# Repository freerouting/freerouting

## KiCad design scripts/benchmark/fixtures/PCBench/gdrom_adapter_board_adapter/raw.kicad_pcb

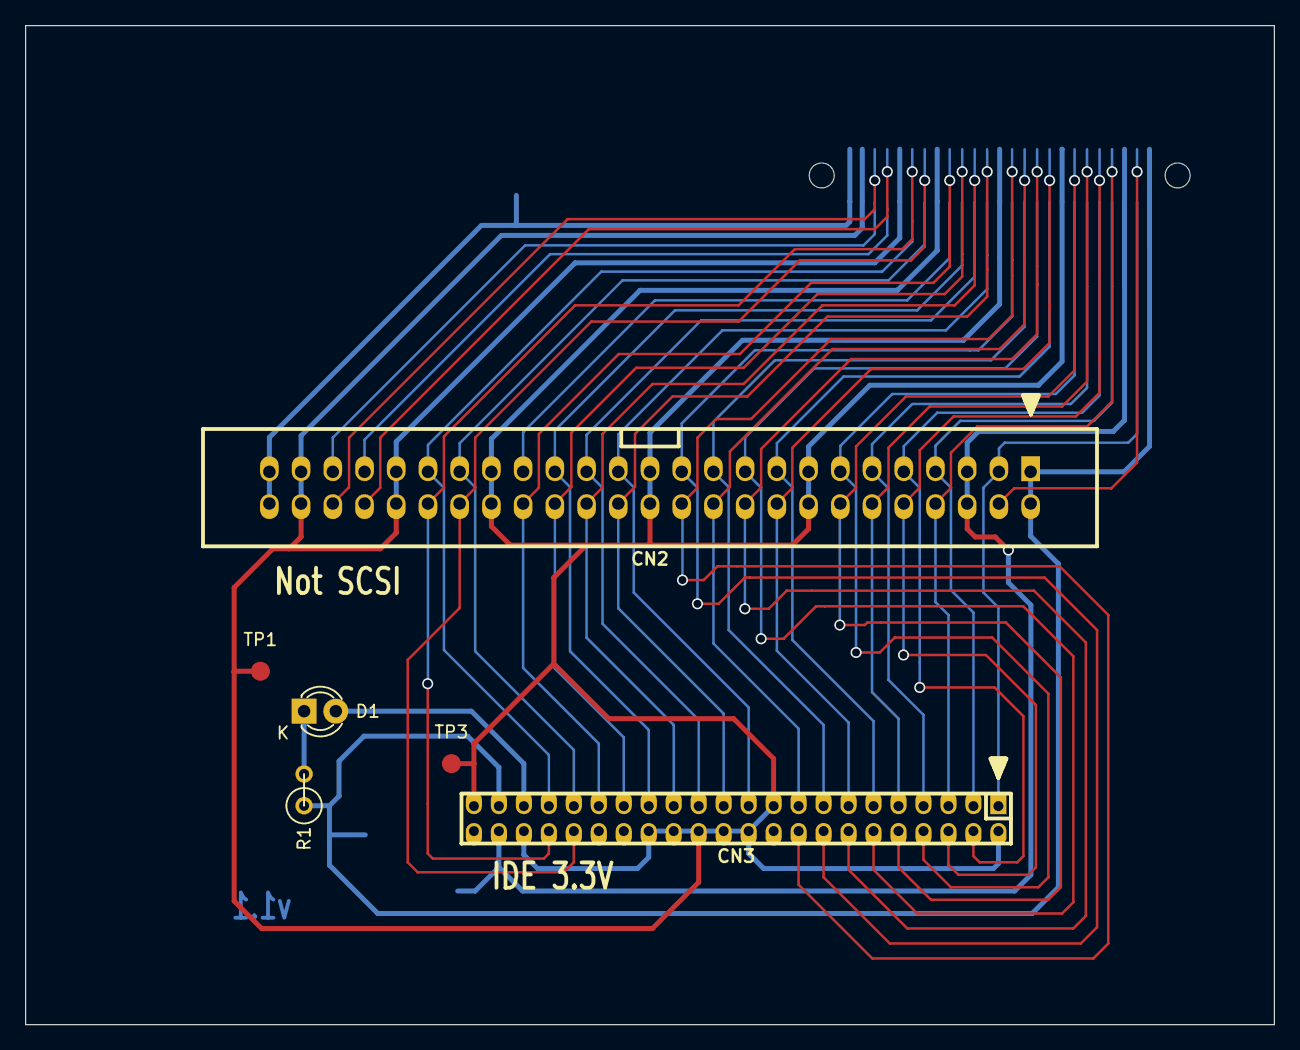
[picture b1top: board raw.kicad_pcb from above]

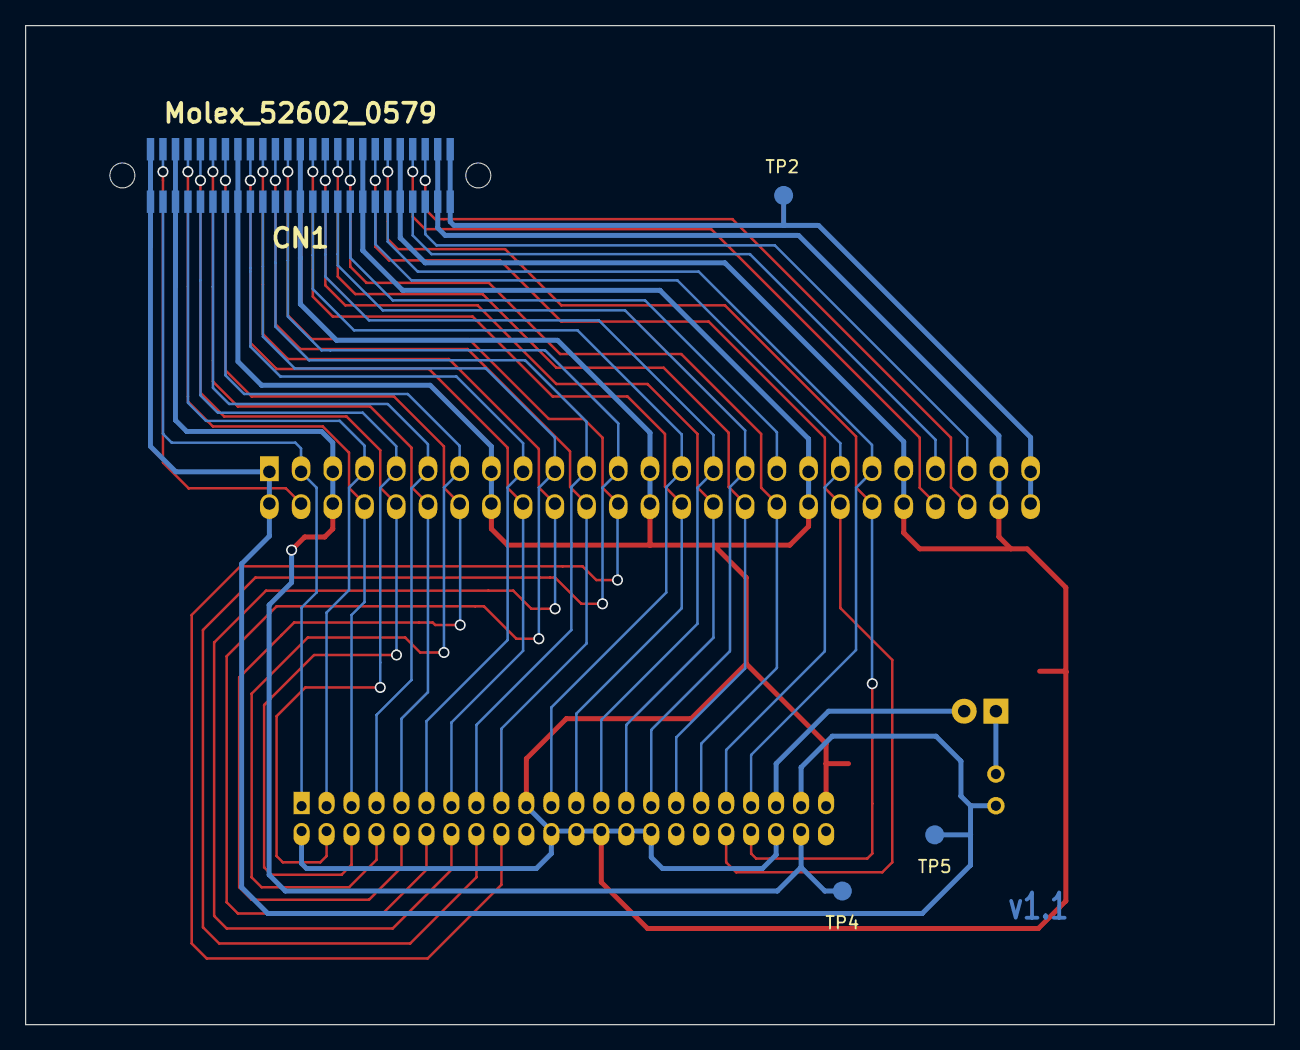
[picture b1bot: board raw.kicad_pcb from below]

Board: 2 copper layers, 100.0 x 80.0 mm, 10 parts (4 on the bottom side), 40 nets.

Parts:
CN1: Molex_52602_0579
CN2: CONN_25X2; vasch_strip_25x2
CN3: CONN_02X22; pin_strip_2mm_22x2
D1: LED; LED-3MM
R1: 1k; R1
TP1, TP2, TP3, TP4, TP5: Measurement_Point_Round-SMD-Pad_Small

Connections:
+3V3: CN1.A1, CN1.B1, CN2.1, CN2.2, CN3.41, R1.1, TP5.1
+5V: CN1.A3, CN1.B3, CN2.5, CN2.6, CN3.42, TP4.1
+12V: CN1.A25, CN1.B25, CN2.49, CN2.50, TP2.1
/A0: CN1.A19, CN2.37, CN3.35
/A1: CN1.B17, CN2.34, CN3.33
/A2: CN1.B19, CN2.38, CN3.36
/ACTIVEn: CN3.39, D1.2
/CD_CLK: CN1.B23, CN2.46
/CS0n: CN1.A20, CN2.39, CN3.37
/CS1n: CN1.B20, CN2.40, CN3.38
/D0: CN1.B11, CN2.22, CN3.17
/D1: CN1.A11, CN2.21, CN3.15
/D2: CN1.B9, CN2.18, CN3.13
/D3: CN1.A9, CN2.17, CN3.11
/D4: CN1.B6, CN2.12, CN3.9
/D5: CN1.A6, CN2.11, CN3.7
/D6: CN1.B4, CN2.8, CN3.5
/D7: CN1.A4, CN2.7, CN3.3
/D8: CN1.A5, CN2.9, CN3.4
/D9: CN1.B5, CN2.10, CN3.6
/D10: CN1.A7, CN2.13, CN3.8
/D11: CN1.B7, CN2.14, CN3.10
/D12: CN1.A10, CN2.19, CN3.12
/D13: CN1.B10, CN2.20, CN3.14
/D14: CN1.A12, CN2.23, CN3.16
/D15: CN1.B12, CN2.24, CN3.18
/DMACKn: CN1.A16, CN2.31, CN3.29
/DMARQ: CN1.A14, CN2.27, CN3.21
/EMPH: CN1.A17, CN2.33
/G_RST: CN1.A2, CN2.3, CN3.1
/INTRQ: CN1.B16, CN2.32, CN3.31
/IORDY: CN1.B15, CN2.30, CN3.27
/LRCK: CN1.B22, CN2.44
/RDn: CN1.A15, CN2.29, CN3.25
/SCK: CN1.A22, CN2.43
/SDAT: CN1.A23, CN2.45
/WRn: CN1.B14, CN2.28, CN3.23
/xB2: CN1.B2, CN2.4
GND: CN1.A8, CN1.A13, CN1.A18, CN1.A21, CN1.A24, CN1.B8, CN1.B13, CN1.B18, CN1.B21, CN1.B24, CN2.15, CN2.16, CN2.25, CN2.26, CN2.35, CN2.36, CN2.41, CN2.42, CN2.47, CN2.48, CN3.2, CN3.19, CN3.22, CN3.24, CN3.26, CN3.28, CN3.30, CN3.40, CN3.43, TP1.1, TP3.1
unnamed: D1.1, R1.2

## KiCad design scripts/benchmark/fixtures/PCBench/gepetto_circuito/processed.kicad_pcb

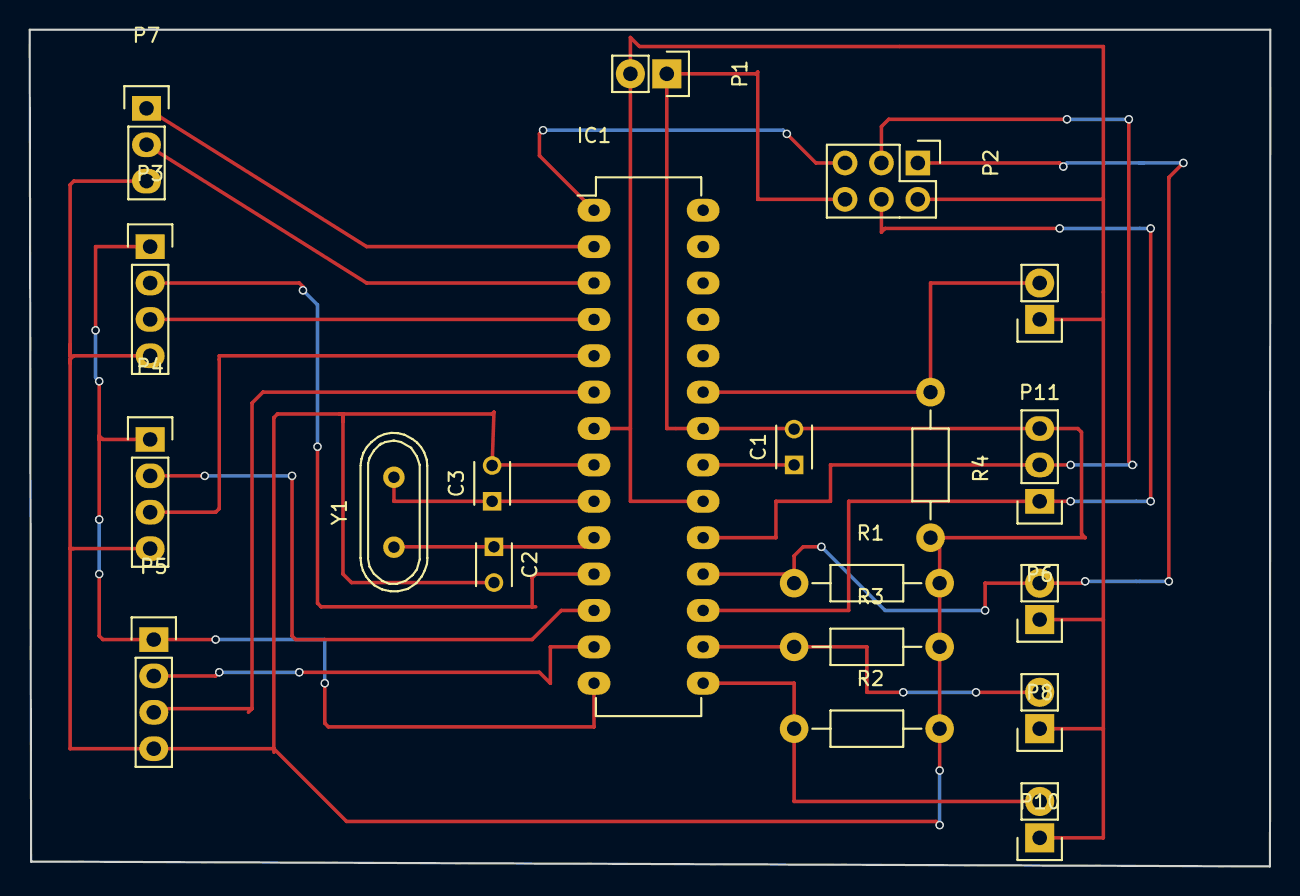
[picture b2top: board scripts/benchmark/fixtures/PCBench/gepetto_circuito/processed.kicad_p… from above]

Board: 2 copper layers, 86.6 x 58.4 mm, 20 parts (0 on the bottom side), 21 nets.

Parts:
C1: 100n; C_Disc_D3_P2.5
C2, C3: 22 pF; C_Disc_D3_P2.5
IC1: ATMEGA328-P; DIP-28_W7.62mm_LongPads
P1: CONN_5V; Pin_Header_Straight_1x02
P2: CONN_02X03; Pin_Header_Straight_2x03
P3: CONN_EJE_X; Pin_Header_Straight_1x04
P4: CONN_EJE_Y; Pin_Header_Straight_1x04
P5: CONN_EJE_Z; Pin_Header_Straight_1x04
P6: CONN_HUS; Pin_Header_Straight_1x03
P7: CONN_UART; Pin_Header_Straight_1x03
P8: CONN_LIM_Z; Pin_Header_Straight_1x02
P9: CONN_LIM_X; Pin_Header_Straight_1x02
P10: CONN_LIM_Y; Pin_Header_Straight_1x02
P11: CONN_E_STOP; Pin_Header_Straight_1x02
R1, R2, R3, R4: 15 k; Resistor_Horizontal_RM10mm
Y1: 16Mhz; Crystal_HC49-U_Vertical

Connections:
/MISO: IC1.18, P2.1, P8.2, R1.1
/MOSI: IC1.17, P2.4, P6.1
/RESET: IC1.1, P2.5
/Rx_int: IC1.2, P7.1
/SCK: IC1.19, P2.3, P6.2
/Tx_int: IC1.3, P7.2
/button_stop: IC1.23, P11.2, R4.1
/dir_X: IC1.11, P3.2
/dir_Y: IC1.12, P4.2
/dir_Z: IC1.13, P5.2
/enable: IC1.14, P3.1, P4.1, P5.1
/lim_X: IC1.15, P9.2, R2.1
/lim_Y: IC1.16, P10.2, R3.1
/step_X: IC1.4, P3.3
/step_Y: IC1.5, P4.3
/step_Z: IC1.6, P5.3
GND: C1.2, C2.2, C3.2, IC1.8, IC1.22, P1.1, P2.6, P3.4, P4.4, P5.4, P6.3, P7.3, R1.2, R2.2, R3.2, R4.2
unnamed: C1.1, IC1.21
unnamed: C2.1, IC1.10, Y1.1
unnamed: C3.1, IC1.9, Y1.2
VCC: IC1.7, IC1.20, P1.2, P2.2, P8.1, P9.1, P10.1, P11.1

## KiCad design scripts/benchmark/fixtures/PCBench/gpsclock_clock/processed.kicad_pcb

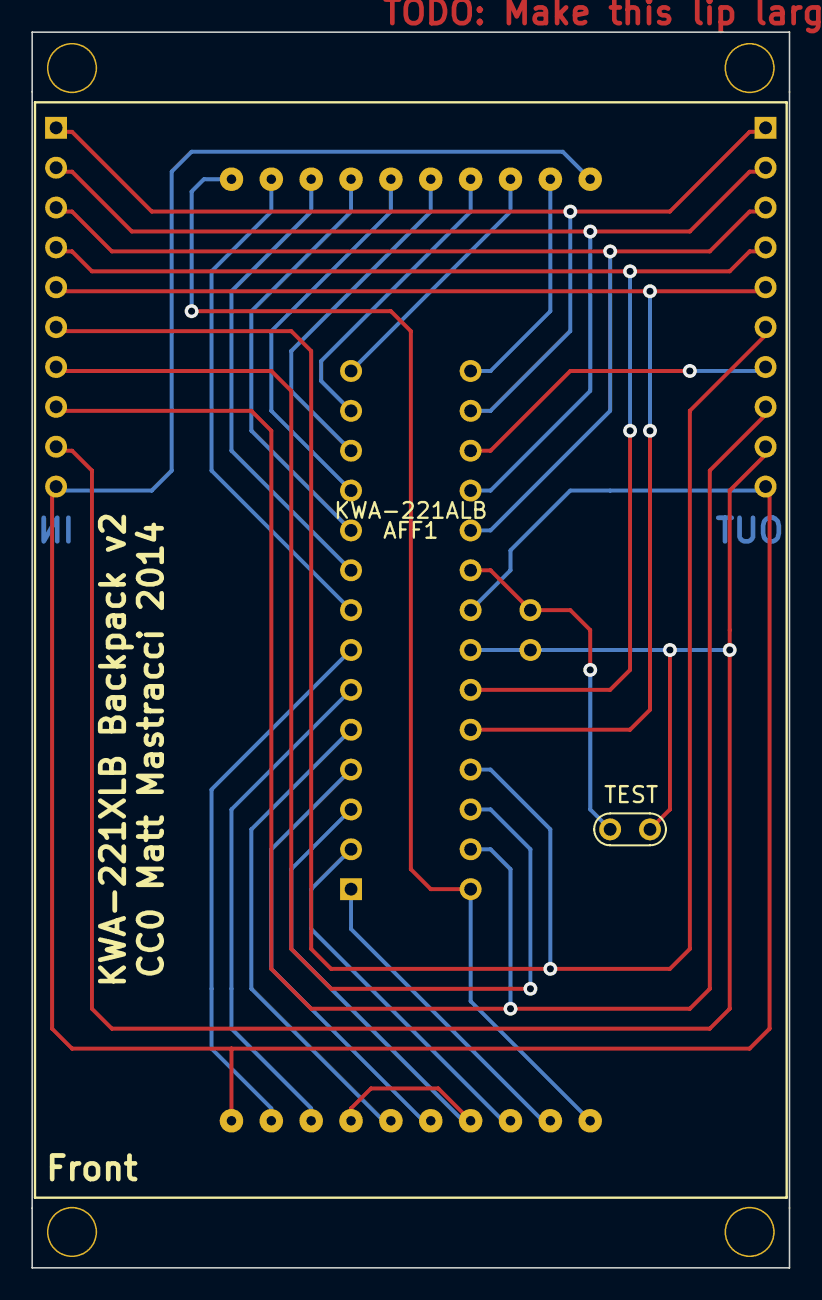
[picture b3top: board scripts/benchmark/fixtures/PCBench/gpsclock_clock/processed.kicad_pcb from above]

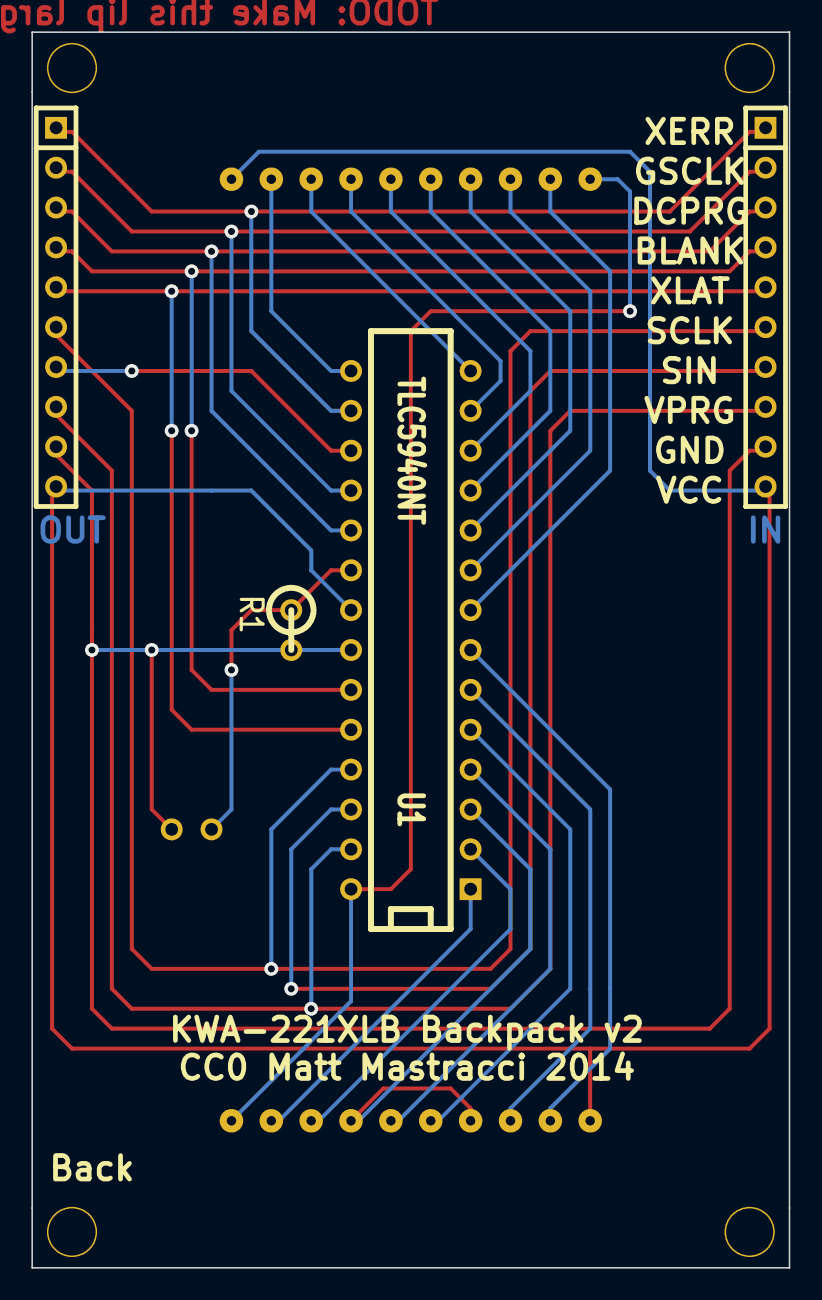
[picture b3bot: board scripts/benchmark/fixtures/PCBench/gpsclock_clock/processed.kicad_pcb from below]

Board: 2 copper layers, 48.3 x 78.7 mm, 10 parts (4 on the bottom side), 28 nets.

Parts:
AFF1: KWA-221ALB; KWA-221
IN1: SIL-10
MH1, MH2, MH3, MH4: MOUNTING_HOLE; 3MM_HOLE
OUT1: SIL-10
R1: R; R1
U1: TLC5940NT; DIP-28__300
W1: TEST; TEST_POINT_2PADS

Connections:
/BLANK: IN1.4, OUT1.4, U1.23
/D0: AFF1.10, AFF1.20, U1.28
/D1: AFF1.9, U1.1
/D2: AFF1.8, U1.2
/D3: AFF1.4, AFF1.7, U1.3
/D4: AFF1.6, U1.4
/D5: AFF1.5, U1.5
/D6: AFF1.3, U1.6
/D7: AFF1.2, U1.7
/D8: AFF1.19, U1.8
/D9: AFF1.18, U1.9
/D10: AFF1.17, U1.10
/D11: AFF1.16, U1.11
/D12: AFF1.15, U1.12
/D13: AFF1.14, U1.13
/D14: AFF1.13, U1.14
/D15: AFF1.12, U1.15
/DCPRG: IN1.3, OUT1.3, U1.19
/GSCLK: IN1.2, OUT1.2, U1.18
/SCLK: IN1.6, OUT1.6, U1.25
/SIN: IN1.7, U1.26
/SOUT: OUT1.7, U1.17
/VPRG: IN1.8, OUT1.8, U1.27
/XERR: IN1.1, OUT1.1, U1.16
/XLAT: IN1.5, OUT1.5, U1.24
GND: IN1.9, OUT1.9, R1.2, U1.22, W1.1
IREF: R1.1, U1.20, W1.2
VCC: AFF1.1, AFF1.11, IN1.10, OUT1.10, U1.21
